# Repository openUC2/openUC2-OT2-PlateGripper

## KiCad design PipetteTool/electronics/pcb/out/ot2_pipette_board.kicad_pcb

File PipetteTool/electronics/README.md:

# Identity board: makes the OT-2 see the ONiLAB tool as a P20 Single-Channel GEN2

No microcontroller is needed for the pipette itself. The OT-2 pipette cable carries everything
the robot needs: I²C to an EEPROM (who is attached), the plunger home switch, and the 4 stepper
wires that the robot's own driver (Allegro A5984, 1/32 microstep, ~36 V) drives directly.

Two ways to answer the robot's EEPROM read:
- **A: a 24C02 EEPROM** (below, "Parts", "Programming the EEPROM"): the cheapest and simplest.
- **B: an ESP32-S3 that pretends to be the EEPROM** (XIAO ESP32-S3 + a BSS138 level shifter,
  section "Option B"): no EEPROM to buy, the ID is set over USB.

## Tool board (V0.5, `pcb/`)

One board, like Opentrons' pipette-main: robot header, identity, motor and switch plugs.

| Part | Value | LCSC | Job |
|---|---|---|---|
| J1 | 2×5 box header, right angle | C9140 | robot ribbon; its face sits 0.55 mm inside the mount face at the plug position |
| U1 | XIAO ESP32-S3 | (hand-fitted) | emulates the EEPROM; on its own pin headers, USB-C toward the open side |
| Q1–Q3, R1–R3 | BSS138, 10 k | C7420339, C25804 | shifters 5 V ↔ 3.3 V for SCL, SDA and MIN (MIN → D3: the XIAO logs the home switch) |
| R6, R7 | 10 k / 15 k | C25804, C22809 | ADDRESS (0 / 5 V) → D0 (0 / 3.0 V) |
| U3 | SRV05-4 | C7420376 | ESD on SCL, SDA, MIN, ADDRESS |
| D1, C2, C3 | B5819W, 10 µF, 100 nF | C8598, C15850, C14663 | ribbon +5 V → XIAO 5V (no back-feed from USB) |
| C1 | 1 nF | C1588 | across the home switch, as on Opentrons' end-stop board |
| J2, J3 | JST-XH 4P / 2P | C144395, C158012 | motor (1 = 1A, 2 = 1B, 3 = 2B, 4 = 2A), switch (COM, NC) |
| U2, C4, R4, R5 | 24C02 SOIC-8, 100 nF, 10 k | C7562, C14663, C25804 | not fitted: option A instead of the XIAO, never both |

- **Build it:** `python pcb/make.py` (KiCad 10 + `uv`). The steps:
  - `netlist.py` (circuit, LCSC numbers) and `layout.py` (placement, board outline, where it sits
    in the tool) go to KiCad;
  - `route.py` routes both layers;
  - pours, DRC, Gerbers and drill files (`out/jlcpcb/gerbers.zip`), `bom.csv` and `cpl.csv` for
    JLCPCB assembly, `out/ot2_pipette_board.step` and the renders.
  - Today: DRC 0 errors, 0 unconnected.
- **Review it** by opening `out/ot2_pipette_board.kicad_pcb` in KiCad 10. There is no schematic
  file yet; the circuit is the table above and `netlist.py`.
- **In the tool:** the board stands upright beside the yoke (+z side), component side toward the
  pipette, and is screwed with 2 × M2 to two tabs under the motor shelf. The frame has the
  window, the plug pocket, the tabs and a 1.8 mm pocket behind the XIAO pins.
- **The XIAO has no socket inside the tool.** A socket adds 5–8.5 mm and would hit the yoke
  disc. Solder it on its supplied pin headers and keep the pins to ≤ 1.5 mm behind the board;
  for a bench board, two 1×7 sockets (C2832270) fit the same pads.
- **Order at JLCPCB:**
  1. Upload `gerbers.zip` (2 layers, 1.6 mm).
  2. For assembly, upload `bom.csv` and `cpl.csv`, then check each part's rotation in their
     viewer, especially the SOT-23s and the headers.
- **Firmware:** `../firmware/ot2_eeprom_emulator_esp32s3` (D4 SDA, D5 SCL, D0 ADDRESS, D3 MIN).

## OT-2 pipette connector (2×5, 2.54 mm, shrouded; 3M 30310-6002HB on Opentrons pipettes)

Checked in Opentrons' published EAGLE files (github.com/Opentrons/ot2, "PCB files"):
`pipette-main.sch` (connector JP1 on the pipette board) and the motor board `5001-stepper-drivers`
(JP4 = left mount, plunger axis B; JP7 = right mount, plunger axis C). Cable length 0.5 m.

| Pin | Net on the robot | Inside an Opentrons pipette | On our tool |
|---|---|---|---|
| 1 | SCL, 5 V I²C (10 k pull-up on the robot) | EEPROM AT24MAC402 SCL | 24C02 pin 6 |
| 2 | SDA, 5 V I²C | EEPROM SDA | 24C02 pin 5 |
| 3 | ADDRESS: tied to GND on the left mount (JP4), to 5 V on the right mount (JP7) | EEPROM A0 → 0x50 / 0x51 | 24C02 pin 1 (A0) |
| 4 | MIN (B_MIN_IN / C_MIN_IN, pulled up on the motor board) | end-stop board: D2F-L COM | switch COM |
| 5 | GND | GND | 24C02 pins 2, 3, 4, 7 (A1, A2, GND, WP); switch NC |
| 6 | +5 V | via a PNP (reverse-polarity switch) to the EEPROM | 24C02 pin 8 (VCC) + 100 nF |
| 7 | MOTOR_2A | motor JST pin 4 | coil B, one end |
| 8 | MOTOR_2B | motor JST pin 3 | coil B, other end |
| 9 | MOTOR_1A | motor JST pin 1 | coil A, one end |
| 10 | MOTOR_1B | motor JST pin 2 | coil A, other end |

```
header on the tool, looking into it (standard IDC numbering, pin 1 = triangle = red stripe)
        ┌──────┐  key  ┌──────┐
        │  1    3    5    7    9  │     SCL   ADDR  GND   M2A   M1A
        │  2    4    6    8   10  │     SDA   MIN   +5V   M2B   M1B
        └─────────────────────────┘
```

Switch: COM → MIN, NC → GND (Opentrons' `pipette-endstop.sch`: D2F-L, 1 nF across). At rest MIN
is held low; pressed (yoke at the top) it opens and the robot's pull-up reads "home".
**Verify pin 1 on your robot before connecting** (checks below).

## Where the robot's plug lands

**V0.5 (checked against Opentrons' OT-2 reference model and app/manual pictures):** on the LEFT
mount the plug's centre is 22.5 mm above the two top screws and 9.3 mm toward the robot front;
on the right mount it sits at the rear (16.5 mm behind the bar centre). The plug sits in a
holder at the top of the mount; together with the round black part, this "top block" stands out
of the mount face. A GEN2 clears it with a pocket around its header and a 5.5 mm recess 38–82 mm
above the screws, and V0.5 copies both. The text below is the V0.2 estimate, kept for the record.

On an Opentrons GEN2 single the 2×5 socket is on the pipette's mount-side face, near one edge
of the 44.5 mm face, with its long side vertical (Science-Jubilee assembly guide photos). The
robot's ribbon comes down the mount bar, is clipped at the bar's top block and its plug is pushed
in sideways just below the gantry cover (OT-2R manual, "attach pipette"). Scaled from the
photos, the socket centre sits about 18-21 mm above the axis of the two top mount screws and
about 9-10 mm from the face edge. V0.2 puts our header 30 mm above those screws (window in the
mount wall, `hdr_y`, `hdr_z` in `cad/pipette_tool.py`) so the board clears the pipette ledge;
the 0.5 m ribbon has slack at its clip. **Measure on the robot and move the window if needed.**

## Motor: YPF Motors 20K-2AB-12.7

Size-8 (20 mm) captive linear stepper, 1 mm lead (stroke 12.7 mm, M2.5 × 5 shaft end, M2 holes
on 15.4 mm, connector on one side near the rear). 200 steps → the robot's 3200 µsteps per robot-mm
give **0.5 mm of yoke travel per robot-mm** (6400 µsteps per real mm).

- Measure both coil resistances (pairs: the two wires with a few Ω between them) and look up or
  ask YPF for the rated current. `ot2/onilab_tool.py` sets run 0.5 A; the robot's GEN2 idle 0.3 A
  and homing 1.0 A cannot be changed (homing lasts a few seconds).
- Coil A → pins 9/10, coil B → pins 7/8. If the yoke moves down when homing, swap 7 ↔ 8.
- The connector sits on the −z side in the frame. Use a right-angle plug or solder the leads; a
  straight plug sticks ~5 mm out of the bar depth.

## Parts

| Qty | Part | Note |
|---|---|---|
| 1 | 24C02 EEPROM, SOIC-8 or DIP-8 (AT24C02, M24C02, ...) | 8-byte pages; any 2 kbit 24xx works |
| 1 | 2×5 shrouded header 2.54 mm | through the window in the mount wall, facing the mount |
| 1 | 100 nF ceramic | |
| 1 | Omron D2F-L or similar 12.8 × 5.8 × 6.5 mm lever micro switch | 2 × M2 self-tapping into the wall |
| 1 | JST-XH 4-pin + 2-pin | motor and switch |
| 1 | perfboard ~33 × 11 mm | 2 × M2.5 self-tapping into the wall (holes 27.9 mm apart, above and below the header) |

## Programming the EEPROM

Use `../firmware/ot2_eeprom_writer/ot2_eeprom_writer.ino` on a Seeed XIAO (RP2040 or SAMD21) or any
Arduino, off the robot, with the EEPROM powered from 3.3 V and A0 to GND (wiring in the sketch).
It writes the layout SmoothiewareOT expects: `opentron` signature at 0x00, ID at 0x30, model
`p20_single_v2.2` at 0x60. Give every tool its own ID: the robot stores calibration and the
plunger settings under it. (Opentrons pipettes keep WP high with 1 k and two buttons; tying WP
to GND is fine, the robot does not write the EEPROM in normal use.)

## Option B: an ESP32-S3 instead of the EEPROM

Yes, this works. The robot only ever **reads** the EEPROM, and in a way an I²C slave can follow
easily. SmoothiewareOT (`src/modules/utils/instrument/Instrument.cpp`) runs the bus at **10 kHz**.
Every access is two separate transactions: it writes the 1-byte memory pointer (STOP), waits
10 ms, then reads 8 bytes (STOP) and waits 10 ms. M369 checks the 8-byte `opentron` signature
at 0x00, then reads the ID 0x30–0x4F; M371 reads the model at 0x60. The 7-bit addresses are
0x50 (left) and 0x51 (right). The robot writes only on M370 / M372 / M374 (pointer + 8 bytes),
which normal use does not send.

On the ESP32-S3, arduino-esp32 (checked in 3.3.12, `esp32-hal-i2c-slave.c`) holds SCL low after a
read request until `onRequest()` has filled the TX FIFO, and drops unread bytes at the STOP. So
the sketch `../firmware/ot2_eeprom_emulator_esp32s3/` only has to:
- keep the pointer from the 1-byte write;
- answer 8 bytes from a 256-byte image;
- store 9-byte writes, persisted in NVS like an EEPROM.

It compiles for `esp32:esp32:XIAO_ESP32S3` with arduino-esp32 3.3.12. **It is not yet tested on
hardware.** The classic ESP32 cannot hold the clock this way: use an S2/S3/C3-class chip.

| Ribbon pin | Goes to | Note |
|---|---|---|
| 6 (+5 V) | XIAO 5V pin, shifter HV | ~30 mA at 80 MHz, radio off (estimate; measure pin 6 under load, see below) |
| 5 (GND) | XIAO GND, shifter GND, divider bottom | |
| — | XIAO 3V3 → shifter LV | |
| 1 (SCL) | shifter HV1, LV1 → XIAO D5 (GPIO6) | **the bus is 5 V with 10 k pull-ups on the robot: never wire it straight to the ESP32** |
| 2 (SDA) | shifter HV2, LV2 → XIAO D4 (GPIO5) | |
| 3 (ADDRESS) | 10 k → XIAO D0 (GPIO1), 15 k from D0 to GND | 0 V = left → 0x50, 5 V → 3.0 V = right → 0x51; read at boot |
| 4, 7–10 | switch and motor, as in option A | the XIAO is not involved |

Parts beyond option A's header, switch and JST plugs:
- 1 × XIAO ESP32-S3.
- 1 × BSS138 2-channel level shifter. Any "I²C logic level converter" board works; its 10 k
  pull-ups in parallel with the robot's give ~5 k, which is fine at 10 kHz. Two BSS138s and
  four 10 k resistors on the perfboard work too.
- Resistors: 10 k and 15 k.

The 24C02 and its 100 nF are not needed.

**Setting it up**

1. Flash the sketch over USB. Open the serial monitor (115200, LF): `show` prints the address,
   ID and model. Every board starts with its own ID derived from the chip's MAC
   (`P20SV22` + 10 digits). `id <text>` sets your own; `model p20_single_v2.2` is the default.
   The robot stores the plunger settings and calibration under the ID.
2. Bench test without the robot: run `../firmware/ot2_eeprom_writer` on a second board as the
   I²C master. It reads exactly like the robot. Wire it directly at 3.3 V (SDA, SCL, GND,
   4.7 k pull-ups to 3V3; leave the emulator's D0 low). `r` must print `signature: ok` with the
   ID and model.
3. On the robot: first measure pin 6 with the board attached; it must stay above 4.75 V. Pin 6
   was meant for an EEPROM behind a PNP, and its current budget is not documented. If it sags,
   power the XIAO from the robot's USB (as the plate gripper does) and keep only GND, I²C and
   ADDRESS on the ribbon. The XIAO boots in well under a second; the robot reads the EEPROM when
   it scans instruments (start-up, homing, protocol start, App refresh). Then continue with the
   checks below. `GET http://<robot-ip>:31950/instruments` (header `Opentrons-Version: 3`)
   shows the model and ID the robot read.

**Where it sits**: not in the CAD yet. Two places look free. Both stay within the GEN2 outline,
and neither has been checked against the parts in CAD yet:
- A 4.5 mm pocket in the mount wall's inner face, between the header board and the motor
  shelf (y ≈ 93–114, +z side, opposite the switch). The yoke disc passes ~0.9 mm away.
- Flat on top of the motor under a small printed cap: 11.6 mm headroom up to the
  estimated GEN2 top datum, so this waits for the datum measurement.

## Checks on the robot before plugging the tool in

1. Unplug the ribbon from a real pipette. Measure 5 V between pins 6 and 5 (red stripe = pin 1).
2. Pin 3 to pin 5: 0 V on the left mount, 5 V on the right mount.
3. Tool side: each motor coil pair reads its rated resistance; no short between coils.
4. Plug in, open the Opentrons App → the mount should show **P20 Single-Channel GEN2**.
5. Home: the yoke must move **up** toward the switch. If it moves down, swap one coil pair (7 ↔ 8).

## Why not the XIAO on I²C or USB for the plunger

- The I²C bus only carries the identity. The robot reads it while scanning instruments (10 kHz,
  8-byte chunks, both plunger motors switched off during each read). It never sends motion over it.
- The plunger axis is a normal stepper axis of the robot's motion controller. Driving our motor from
  those 4 wires gives native `aspirate / dispense / blow_out / home`, the App, Protocol Designer and
  calibration without any extra firmware.

## A second motor for the tip ejector (if over-travel is not used)

No board has to interpret the plunger steps. A second switch that the yoke reaches only below
blow-out (only `drop_tip()` goes there) tells a XIAO to run the ejector motor; a slow
`dropTipSpeed` over the last robot-mm gives it the time. Power: pin 6 is on whenever the robot is
on, but it feeds Opentrons' pipette board through a small PNP and its current budget is not
documented, so do not run a motor from it. USB from the robot (as the plate gripper does) gives
5 V / 0.5 A and a serial line. Options for the XIAO beyond that: plain serial from the protocol,
or imitating a Magnetic Module (VID:PID 04d8:ee90, `G28.2`, `G0 Z`, `M114.2`, `M115`).

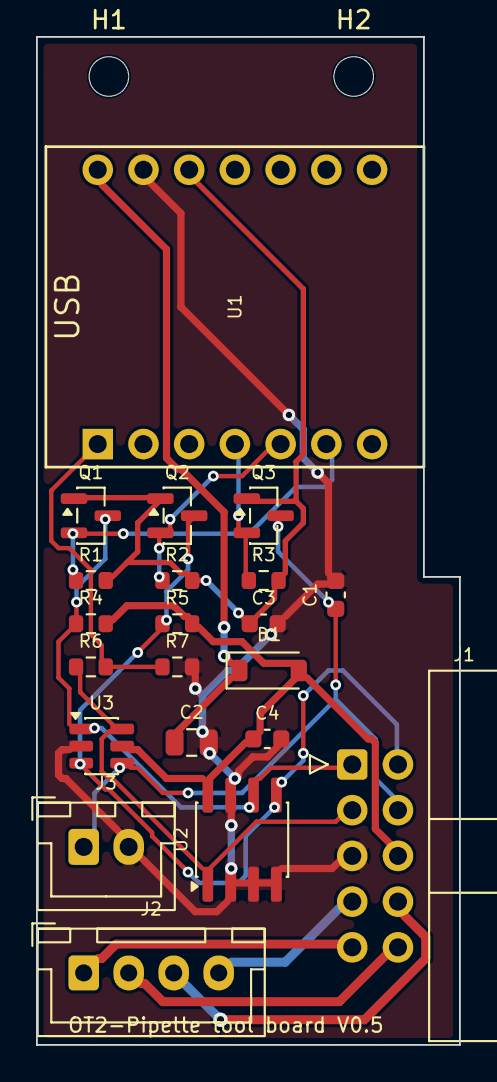
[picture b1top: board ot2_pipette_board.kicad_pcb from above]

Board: 2 copper layers, 23.5 x 56.0 mm, 23 parts (0 on the bottom side), 16 nets.

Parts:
C1: 1nF; C_0603_1608Metric
C2: 10uF; C_0805_2012Metric
C3, C4: 100nF; C_0603_1608Metric
D1: B5819W; D_SOD-123
H1, H2: MountingHole_2.2mm_M2
J1: 2x5 box header, right angle; IDC-Header_2x05_P2.54mm_Horizontal
J2: JST XH 4P motor; JST_XH_B4B-XH-A_1x04_P2.50mm_Vertical
J3: JST XH 2P switch; JST_XH_B2B-XH-A_1x02_P2.50mm_Vertical
Q1, Q2, Q3: BSS138; SOT-23
R1, R2, R3, R4, R5, R6: 10k; R_0603_1608Metric
R7: 15k; R_0603_1608Metric
U1: XIAO ESP32-S3 on its pin headers; XIAO_ESP32S3_Socket_2x1x7
U2: 24C02; SOIC-8_3.9x4.9mm_P1.27mm
U3: SRV05-4; SOT-23-6

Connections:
+3V3: C3.1, Q1.1, Q2.1, Q3.1, R1.2, R2.2, R3.2, U1.12
+5V: C4.1, D1.2, J1.6, R4.2, R5.2, U2.8, U3.5
+5VX: C2.1, D1.1, U1.14
ADDR: J1.3, R6.1, U2.1, U3.6
A_SENSE: R6.2, R7.1, U1.1
GND: C1.2, C2.2, C3.2, C4.2, J1.5, J3.2, R7.2, U1.13, U2.2, U2.3, U2.4, U2.7, U3.2
M1A: J1.9, J2.1
M1B: J1.10, J2.2
M2A: J1.7, J2.4
M2B: J1.8, J2.3
MIN: C1.1, J1.4, J3.1, Q3.3, U3.4
MIN3: Q3.2, R3.1, U1.4
SCL3: Q1.2, R1.1, U1.6
SCL5: J1.1, Q1.3, R4.1, U2.6, U3.1
SDA3: Q2.2, R2.1, U1.5
SDA5: J1.2, Q2.3, R5.1, U2.5, U3.3

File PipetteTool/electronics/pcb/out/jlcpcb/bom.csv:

Comment,Designator,Footprint,LCSC Part #
100nF,C3,C_0603_1608Metric,C14663
10k,"R1,R2,R3,R6",R_0603_1608Metric,C25804
10uF,C2,C_0805_2012Metric,C15850
15k,R7,R_0603_1608Metric,C22809
1nF,C1,C_0603_1608Metric,C1588
"2x5 box header, right angle",J1,IDC-Header_2x05_P2.54mm_Horizontal,C9140
B5819W,D1,D_SOD-123,C8598
BSS138,"Q1,Q2,Q3",SOT-23,C7420339
JST XH 2P switch,J3,JST_XH_B2B-XH-A_1x02_P2.50mm_Vertical,C158012
JST XH 4P motor,J2,JST_XH_B4B-XH-A_1x04_P2.50mm_Vertical,C144395
SRV05-4,U3,SOT-23-6,C7420376
